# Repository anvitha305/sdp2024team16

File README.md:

# sdp2024team16 - Evaluation of the Inertial Measurement Units (IMUs) we Wanted to Use

Our team has run an evaluation on all the available IMU models at both makerspaces to determine which ones would be the best for our purposes.

## BMI160+BMM150 Shuttleboard
Prior to our determination that we wanted onboard processing capability as a feature for the IMUs, we selected this IMU due to its resolution being on the same order as the BNO055 (a Zero-Offset error of +- 1-2 degrees per second with a 250 degrees per second system), and its power consumption being on the order of 100s of microamps as opposed to milliamps, since we were cognizant of the implications of needing multiple sensors on one bow that were heavily power-consuming. However, this shuttleboard is obsolete, which speaks to the fact that there is improved technology in the field for the same purposes, and there is currently a lack of support from Bosch (the manufacturer of these IMUs) and to prototype with these boards we would need to write our own processing algorithm for handling the data received from this sensor, which would add an extensive amount of effort to a section of the project which is not a priority as it is not the novel component of the project.

## LSM9DS1 
After determining our issues with the shuttleboard, we decided to pivot to analyzing two variants of IMUs with onboard processing capabilities. The LSM9DS1 was one of two available options with this criteria. We evaluated with a compass and the archery range that an accuracy of ~1-2 degrees per second in a 250 degrees per second system was the specification that worked best in our case with maintaining aim accuracy. We decided that triangulating IMUs on varying positions of the bow would facilitate improving accuracy because it would enable us to get multiple perspectives on the direction of the arrow and improve the aim of the user.  The information about the LSM9DS1’s accuracy does not provide a small range of expected accuracy, stating  <30dps with a 250dps system according to the datasheet, which lead us to believe that the accuracy of the LSM9DS1 would not likely fit our specifications that we outlined in Section D. Further, the typical power draw was 4.3mA for the LSM9DS1.

## BNO055
In conclusion of our initial analysis of the Inertial Measurement Units for this project, we have chosen the BNO055, as its accuracy is on the order of the Bosch BMI160 and BMM150 shuttleboard while having onboard processing capabilities, both of which are on the order we analyzed to be acceptable for our purposes. We found that its low power mode provided a typical draw of 2.7mA, compromising the sensor reading rate as a result, and its typical draw on average was 3.1mA, which is considerably higher than the shuttleboard but understandable due to the convenience that it affords us.

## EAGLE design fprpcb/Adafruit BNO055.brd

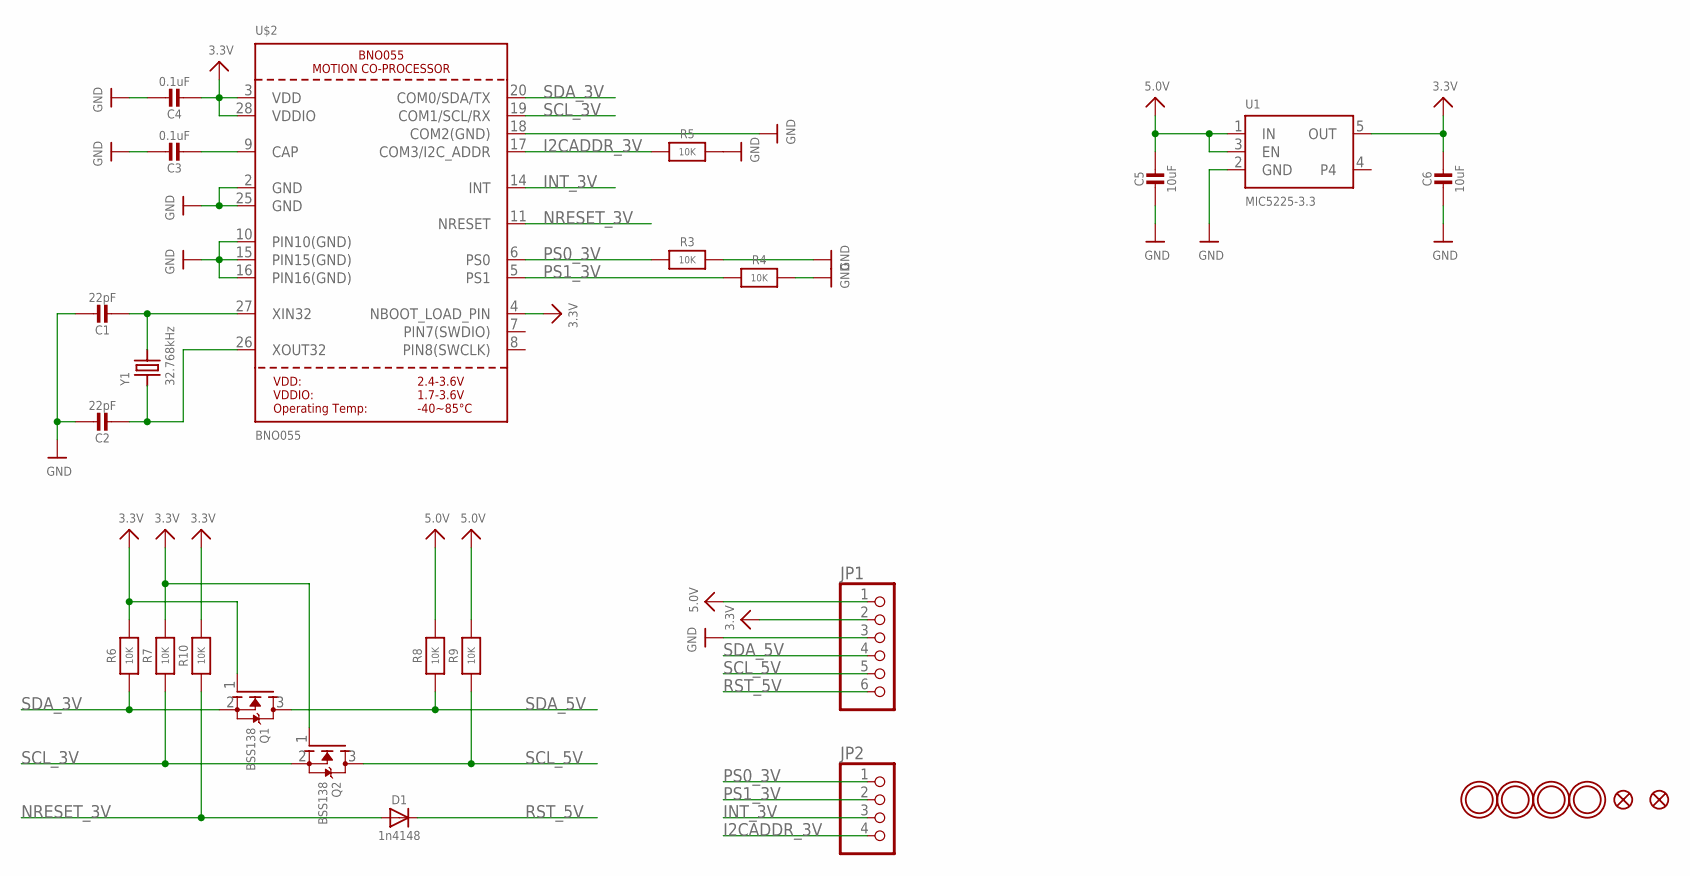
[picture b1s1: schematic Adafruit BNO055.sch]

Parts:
C1, C2: 22pF; 0805-NO
C3: 0.1uF; 0805-NO
C4: 0.1uF; 0805_10MGAP
C5: 10uF; 0805-NO
C6: 10uF; 0805_10MGAP
D1: 1n4148; SOD-323
FID1, FID2: FIDUCIAL""; FIDUCIAL_1MM
JP1: HEADER-1X676MIL; 1X06_ROUND_76
JP2: HEADER-1X476MIL; 1X04_ROUND_76
Q1, Q2: BSS138; SOT23-WIDE
R3, R4, R5, R6, R7, R10: 10K; 0805-NO
R8, R9: 10K; _0805MP
U1: MIC5225-3.3; SOT23-5
U$2: BNO055
U$29, U$30, U$31, U$32: MOUNTINGHOLE2.5_THICK; MOUNTINGHOLE_2.5_PLATED_THICK
Y1: 32.768kHz; CRYSTAL_8X3.8

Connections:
3.3V: C4.2, C6.1, JP1.2, Q1.1 (G), Q2.1 (G), R6.2, R7.2, R10.2, U1.5 (OUT), U$2.3 (VDD), U$2.4 (NBOOT_LOAD_PIN), U$2.28 (VDDIO)
5.0V: C5.1, JP1.1, R8.2, R9.2, U1.1 (IN), U1.3 (EN)
GND: C1.1, C2.1, C3.1, C4.1, C5.2, C6.2, JP1.3, R3.2, R4.2, R5.2, U1.2 (GND), U$2.2 (GND), U$2.10 (PIN10(GND)), U$2.15 (PIN15(GND)), U$2.16 (PIN16(GND)), U$2.18 (COM2(GND)), U$2.25 (GND)
I2CADDR_3V: JP2.4, R5.1, U$2.17 (COM3/I2C_ADDR)
INT_3V: JP2.3, U$2.14 (INT)
unnamed: C1.2, U$2.27 (XIN32), Y1.P$4 (2)
unnamed: C2.2, U$2.26 (XOUT32), Y1.P$1 (1)
unnamed: C3.2, U$2.9 (CAP)
NRESET_3V: D1.A, R10.1, U$2.11 (NRESET)
PS0_3V: JP2.1, R3.1, U$2.6 (PS0)
PS1_3V: JP2.2, R4.1, U$2.5 (PS1)
RST_5V: D1.C, JP1.6
SCL_3V: Q2.2 (S), R7.1, U$2.19 (COM1/SCL/RX)
SCL_5V: JP1.5, Q2.3 (D), R9.1
SDA_3V: Q1.2 (S), R6.1, U$2.20 (COM0/SDA/TX)
SDA_5V: JP1.4, Q1.3 (D), R8.1

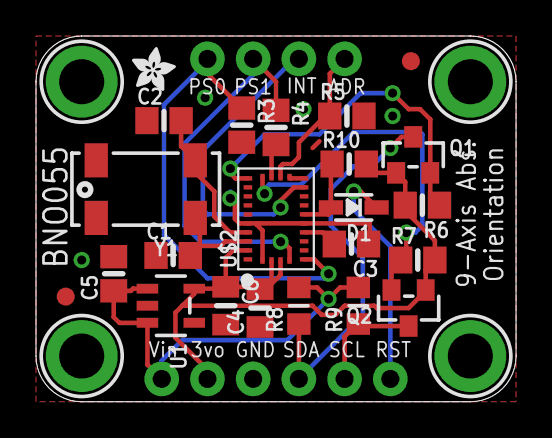
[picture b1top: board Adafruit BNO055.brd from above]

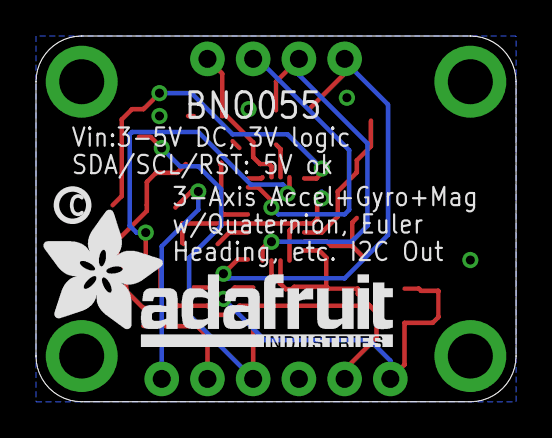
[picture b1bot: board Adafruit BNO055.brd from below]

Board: 2 copper layers, 26.7 x 20.3 mm, 31 parts (2 on the bottom side), 16 nets.

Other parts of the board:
U$3: PCBFEAT-REV-040
U$28: ADAFRUIT_TEXT_20MM
U$33: ADAFRUIT_2.5MM

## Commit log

2023-09-28 imu test for the BMI160
2023-10-04 adding to the readme
2023-10-21 IMU info
2023-11-06 completed repo
2023-11-13 Added numerical solver script
2023-11-13 Integrated ballistics script into simulator
2023-11-14 Switched to 4th order diffeq calculations
2023-11-15 Display Interval =/= Calculation Interval
2023-11-17 Some optimizations
2023-11-29 Create DisplayButtons
2023-11-29 Create DisplayTest
2023-11-29 Create PerspectiveProjection
2023-12-03 better and newer imu code :))
2023-12-03 Update PerspectiveProjection
2023-12-03 Update sim.py
    Integrating the simulator with the arduino stuff :)
2024-02-21 Added cdrpcb1
2024-02-21 Added latest display code
2024-02-24 cdrpcb2
2024-02-27 update cdrpcb
    bno055 footprints
2024-02-28 cdrpcb3
    Started routing
2024-03-01 cdrpcb4
    Routed the PCB
2024-03-02 cdrpcb5
    centered the mounting holes
2024-03-02 Re-routed with increased pwr/gnd thickness and overall clearance
2024-03-03 add labels, fix charging circuit traces
2024-03-03 widened traces, fixed charging circuit (for real)
2024-03-04 fixing mounting hole distancing and spacing issues and also adding in custom 5.0mm footprint for holes in KiCad
2024-03-04 cdrpcb Final
    added the gerber files
2024-03-06 Added ino of integrated code, needs testing
2024-03-08 Update MainDisplayIntegrated.ino
    change SPI chip select pin for the eeprom
2024-03-08 Update MainDisplayIntegrated.ino
    changed the pins to resolve EEPROM + display conflict
2024-03-10 Battery code
2024-03-12 PCB iteration with download, drill and appropriately named schematic
2024-03-12 Working RP2040 Integrated Code
2024-03-12 Bill of Materials for assembly of PCB
2024-03-28 FPR PCB Iter. 1
    Fixed stuff from CDR report
2024-03-29 updated fprpcb
2024-03-29 fixed power switch issue where ghost components were showing up on the board
2024-03-29 fprpcb (again and fr this time 💀)
2024-03-29 fprpcb
2024-03-29 SDP teams FPRPCB
2024-03-30 Revert "fprpcb"
    This reverts commit a24959e1a84143555ed98c59d3b6709d6d6878c6.
2024-03-31 fixed the errors described by Tyler on 3/29 morning
2024-03-31 update repo with true PCB that has all the fixed ones because the old one only updated the schematic
    💀💀💀💀💀💀💀
2024-03-31 Clean up gross track ends
    little itty bitty track ends are the death of me 💀
2024-03-31 verifying all traces to be correct size and clearance
2024-03-31 Updated FPRPCB based on 3/30 feedback
2024-04-10 fprpcb.csv
    bill of materials for the fprpcb
2024-04-22 Updated with Working Code from Apr 21 (IMUs currently spewing incorrect data)
2024-04-23 Update MainDisplayIntegrated.ino
    Updated for acceleration due to grav 💀
2024-04-24 Almost done :)
2024-04-25 Updated UI

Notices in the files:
parts and their libraries:
microbuilder: This work is placed in the public domain, and may be freely used for commercial and non-commercial work with the following conditions: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
